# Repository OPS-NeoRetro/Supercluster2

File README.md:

# 160-Core RV32EC M.2 Supercluster

---

This supercluster consists of 10 vertically-mounted M.2 2230 modules containing 16 CH32V203C8T6 microcontrollers (not compatible with real M.2 slots) on an M.2 2280 baseboard. Host-to-cluster communication goes through a PCI Express UART controller connected to a CH32V208 on the bottom of the baseboard. Communications inside the cluster go through a custom bus that connects all 160 CH32V203 nodes and the CH32V208 baseboard controller together. Click the image below to watch the YouTube video explaining this supercluster's origins.

## Photos

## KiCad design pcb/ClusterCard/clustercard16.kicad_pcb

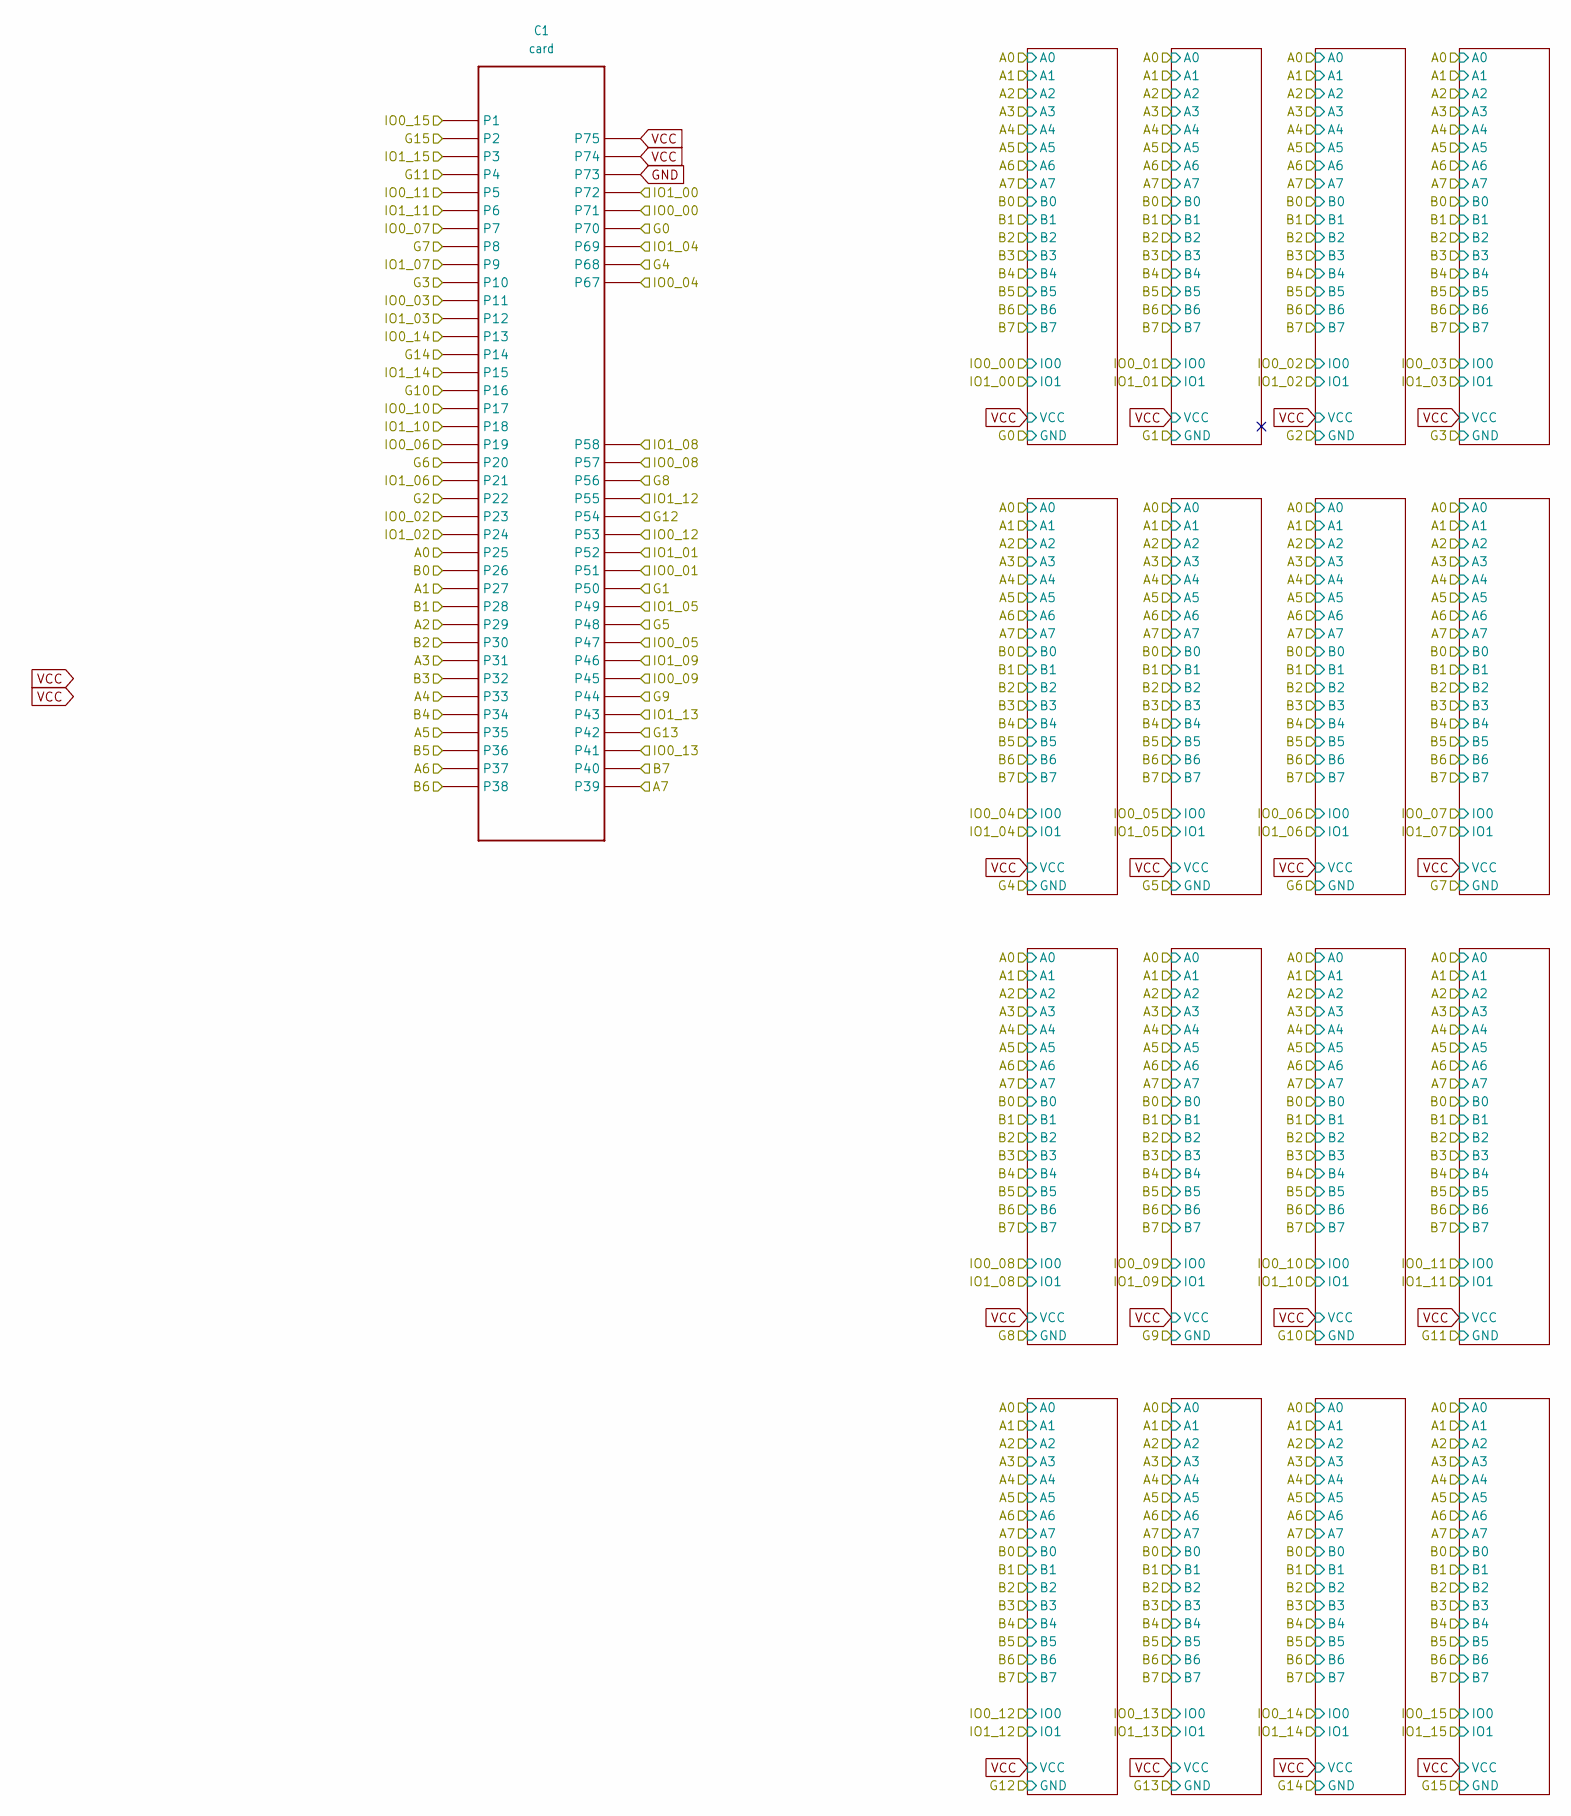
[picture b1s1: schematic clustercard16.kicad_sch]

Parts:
C1: card; M.2-M-KEY cluster card

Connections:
/A0: C1.P$25 (P25); also elsewhere on the board
/A1: C1.P$27 (P27); also elsewhere on the board
/A2: C1.P$29 (P29); also elsewhere on the board
/A3: C1.P$31 (P31); also elsewhere on the board
/A4: C1.P$33 (P33); also elsewhere on the board
/A5: C1.P$35 (P35); also elsewhere on the board
/A6: C1.P$37 (P37); also elsewhere on the board
/A7: C1.P$39 (P39); also elsewhere on the board
/B0: C1.P$26 (P26); also elsewhere on the board
/B1: C1.P$28 (P28); also elsewhere on the board
/B2: C1.P$30 (P30); also elsewhere on the board
/B3: C1.P$32 (P32); also elsewhere on the board
/B4: C1.P$34 (P34); also elsewhere on the board
/B5: C1.P$36 (P36); also elsewhere on the board
/B6: C1.P$38 (P38); also elsewhere on the board
/B7: C1.P$40 (P40); also elsewhere on the board
/G0: C1.P$70 (P70); also elsewhere on the board
/G1: C1.P$50 (P50); also elsewhere on the board
/G2: C1.P$22 (P22); also elsewhere on the board
/G3: C1.P$10 (P10); also elsewhere on the board
/G4: C1.P$68 (P68); also elsewhere on the board
/G5: C1.P$48 (P48); also elsewhere on the board
/G6: C1.P$20 (P20); also elsewhere on the board
/G7: C1.P$8 (P8); also elsewhere on the board
/G8: C1.P$56 (P56); also elsewhere on the board
/G9: C1.P$44 (P44); also elsewhere on the board
/G10: C1.P$16 (P16); also elsewhere on the board
/G11: C1.P$4 (P4); also elsewhere on the board
/G12: C1.P$54 (P54); also elsewhere on the board
/G13: C1.P$42 (P42); also elsewhere on the board
/G14: C1.P$14 (P14); also elsewhere on the board
/G15: C1.P$2 (P2); also elsewhere on the board
/IO0_00: C1.P$71 (P71); also elsewhere on the board
/IO0_01: C1.P$51 (P51); also elsewhere on the board
/IO0_02: C1.P$23 (P23); also elsewhere on the board
/IO0_03: C1.P$11 (P11); also elsewhere on the board
/IO0_04: C1.P$67 (P67); also elsewhere on the board
/IO0_05: C1.P$47 (P47); also elsewhere on the board
/IO0_06: C1.P$19 (P19); also elsewhere on the board
/IO0_07: C1.P$7 (P7); also elsewhere on the board
/IO0_08: C1.P$57 (P57); also elsewhere on the board
/IO0_09: C1.P$45 (P45); also elsewhere on the board
/IO0_10: C1.P$17 (P17); also elsewhere on the board
/IO0_11: C1.P$5 (P5); also elsewhere on the board
/IO0_12: C1.P$53 (P53); also elsewhere on the board
/IO0_13: C1.P$41 (P41); also elsewhere on the board
/IO0_14: C1.P$13 (P13); also elsewhere on the board
/IO0_15: C1.P$1 (P1); also elsewhere on the board
/IO1_00: C1.P$72 (P72); also elsewhere on the board
/IO1_01: C1.P$52 (P52); also elsewhere on the board
/IO1_02: C1.P$24 (P24); also elsewhere on the board
/IO1_03: C1.P$12 (P12); also elsewhere on the board
/IO1_04: C1.P$69 (P69); also elsewhere on the board
/IO1_05: C1.P$49 (P49); also elsewhere on the board
/IO1_06: C1.P$21 (P21); also elsewhere on the board
/IO1_07: C1.P$9 (P9); also elsewhere on the board
/IO1_08: C1.P$58 (P58); also elsewhere on the board
/IO1_09: C1.P$46 (P46); also elsewhere on the board
/IO1_10: C1.P$18 (P18); also elsewhere on the board
/IO1_11: C1.P$6 (P6); also elsewhere on the board
/IO1_12: C1.P$55 (P55); also elsewhere on the board
/IO1_13: C1.P$43 (P43); also elsewhere on the board
/IO1_14: C1.P$15 (P15); also elsewhere on the board
/IO1_15: C1.P$3 (P3); also elsewhere on the board
GND: C1.P$73 (P73)
VCC: C1.P$74 (P74), C1.P$75 (P75); also elsewhere on the board

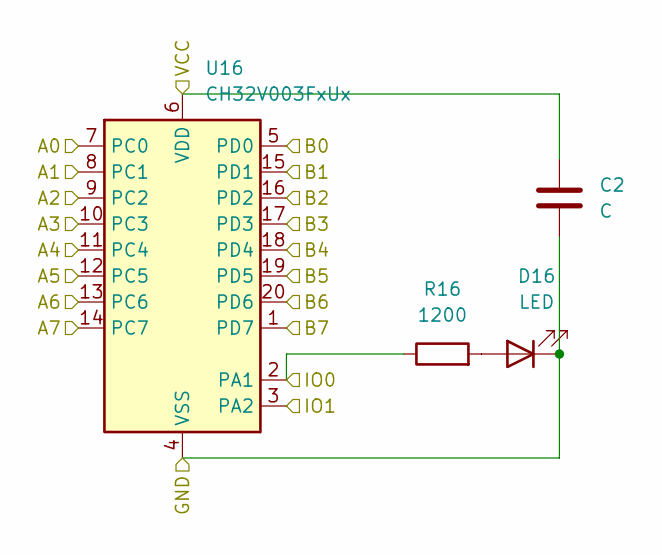
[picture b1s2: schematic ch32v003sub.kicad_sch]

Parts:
C2: C; C_0402_1005Metric
D16: LED; LED_0402_1005Metric
R16: 1200; R_0402_1005Metric
U16: CH32V003FxUx; QFN-20-1EP_3x3mm_P0.4mm_EP1.65x1.65mm_min

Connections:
/A0: U16.7 (PC0); also elsewhere on the board
/A1: U16.8 (PC1); also elsewhere on the board
/A2: U16.9 (PC2); also elsewhere on the board
/A3: U16.10 (PC3); also elsewhere on the board
/A4: U16.11 (PC4); also elsewhere on the board
/A5: U16.12 (PC5); also elsewhere on the board
/A6: U16.13 (PC6); also elsewhere on the board
/A7: U16.14 (PC7); also elsewhere on the board
/B0: U16.5 (PD0); also elsewhere on the board
/B1: U16.15 (PD1); also elsewhere on the board
/B2: U16.16 (PD2); also elsewhere on the board
/B3: U16.17 (PD3); also elsewhere on the board
/B4: U16.18 (PD4); also elsewhere on the board
/B5: U16.19 (PD5); also elsewhere on the board
/B6: U16.20 (PD6); also elsewhere on the board
/B7: U16.1 (PD7); also elsewhere on the board
/G0: C2.2, D16.1 (K), U16.4 (VSS), U16.21 (VSS); also elsewhere on the board
/IO0_00: R16.1, U16.2 (PA1); also elsewhere on the board
/IO1_00: U16.3 (PA2); also elsewhere on the board
unnamed: D16.2 (A), R16.2
VCC: C2.1, U16.6 (VDD); also elsewhere on the board

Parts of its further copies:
C3, C4, C5, C6, C7, C8, C9, C10, C11, C12, C13, C14, C15, C16, C17: C; C_0402_1005Metric
D1, D2, D3, D4, D5, D6, D7, D8, D9, D10, D11, D12, D13, D14, D15: LED; LED_0402_1005Metric
R1, R2, R3, R4, R5, R6, R7, R8, R9, R10, R11, R12, R13, R14, R15: 1200; R_0402_1005Metric
U1, U2, U3, U4, U5, U6, U7, U8, U9, U10, U11, U12, U13, U14, U15: CH32V003FxUx; QFN-20-1EP_3x3mm_P0.4mm_EP1.65x1.65mm_min

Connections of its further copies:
/A0: U1.7 (PC0), U2.7 (PC0), U3.7 (PC0), U4.7 (PC0), U5.7 (PC0), U6.7 (PC0), U7.7 (PC0), U8.7 (PC0), U9.7 (PC0), U10.7 (PC0), U11.7 (PC0), U12.7 (PC0), U13.7 (PC0), U14.7 (PC0), U15.7 (PC0); also elsewhere on the board
/A1: U1.8 (PC1), U2.8 (PC1), U3.8 (PC1), U4.8 (PC1), U5.8 (PC1), U6.8 (PC1), U7.8 (PC1), U8.8 (PC1), U9.8 (PC1), U10.8 (PC1), U11.8 (PC1), U12.8 (PC1), U13.8 (PC1), U14.8 (PC1), U15.8 (PC1); also elsewhere on the board
/A2: U1.9 (PC2), U2.9 (PC2), U3.9 (PC2), U4.9 (PC2), U5.9 (PC2), U6.9 (PC2), U7.9 (PC2), U8.9 (PC2), U9.9 (PC2), U10.9 (PC2), U11.9 (PC2), U12.9 (PC2), U13.9 (PC2), U14.9 (PC2), U15.9 (PC2); also elsewhere on the board
/A3: U1.10 (PC3), U2.10 (PC3), U3.10 (PC3), U4.10 (PC3), U5.10 (PC3), U6.10 (PC3), U7.10 (PC3), U8.10 (PC3), U9.10 (PC3), U10.10 (PC3), U11.10 (PC3), U12.10 (PC3), U13.10 (PC3), U14.10 (PC3), U15.10 (PC3); also elsewhere on the board
/A4: U1.11 (PC4), U2.11 (PC4), U3.11 (PC4), U4.11 (PC4), U5.11 (PC4), U6.11 (PC4), U7.11 (PC4), U8.11 (PC4), U9.11 (PC4), U10.11 (PC4), U11.11 (PC4), U12.11 (PC4), U13.11 (PC4), U14.11 (PC4), U15.11 (PC4); also elsewhere on the board
/A5: U1.12 (PC5), U2.12 (PC5), U3.12 (PC5), U4.12 (PC5), U5.12 (PC5), U6.12 (PC5), U7.12 (PC5), U8.12 (PC5), U9.12 (PC5), U10.12 (PC5), U11.12 (PC5), U12.12 (PC5), U13.12 (PC5), U14.12 (PC5), U15.12 (PC5); also elsewhere on the board
/A6: U1.13 (PC6), U2.13 (PC6), U3.13 (PC6), U4.13 (PC6), U5.13 (PC6), U6.13 (PC6), U7.13 (PC6), U8.13 (PC6), U9.13 (PC6), U10.13 (PC6), U11.13 (PC6), U12.13 (PC6), U13.13 (PC6), U14.13 (PC6), U15.13 (PC6); also elsewhere on the board
/A7: U1.14 (PC7), U2.14 (PC7), U3.14 (PC7), U4.14 (PC7), U5.14 (PC7), U6.14 (PC7), U7.14 (PC7), U8.14 (PC7), U9.14 (PC7), U10.14 (PC7), U11.14 (PC7), U12.14 (PC7), U13.14 (PC7), U14.14 (PC7), U15.14 (PC7); also elsewhere on the board
/B0: U1.5 (PD0), U2.5 (PD0), U3.5 (PD0), U4.5 (PD0), U5.5 (PD0), U6.5 (PD0), U7.5 (PD0), U8.5 (PD0), U9.5 (PD0), U10.5 (PD0), U11.5 (PD0), U12.5 (PD0), U13.5 (PD0), U14.5 (PD0), U15.5 (PD0); also elsewhere on the board
/B1: U1.15 (PD1), U2.15 (PD1), U3.15 (PD1), U4.15 (PD1), U5.15 (PD1), U6.15 (PD1), U7.15 (PD1), U8.15 (PD1), U9.15 (PD1), U10.15 (PD1), U11.15 (PD1), U12.15 (PD1), U13.15 (PD1), U14.15 (PD1), U15.15 (PD1); also elsewhere on the board
/B2: U1.16 (PD2), U2.16 (PD2), U3.16 (PD2), U4.16 (PD2), U5.16 (PD2), U6.16 (PD2), U7.16 (PD2), U8.16 (PD2), U9.16 (PD2), U10.16 (PD2), U11.16 (PD2), U12.16 (PD2), U13.16 (PD2), U14.16 (PD2), U15.16 (PD2); also elsewhere on the board
/B3: U1.17 (PD3), U2.17 (PD3), U3.17 (PD3), U4.17 (PD3), U5.17 (PD3), U6.17 (PD3), U7.17 (PD3), U8.17 (PD3), U9.17 (PD3), U10.17 (PD3), U11.17 (PD3), U12.17 (PD3), U13.17 (PD3), U14.17 (PD3), U15.17 (PD3); also elsewhere on the board
/B4: U1.18 (PD4), U2.18 (PD4), U3.18 (PD4), U4.18 (PD4), U5.18 (PD4), U6.18 (PD4), U7.18 (PD4), U8.18 (PD4), U9.18 (PD4), U10.18 (PD4), U11.18 (PD4), U12.18 (PD4), U13.18 (PD4), U14.18 (PD4), U15.18 (PD4); also elsewhere on the board
/B5: U1.19 (PD5), U2.19 (PD5), U3.19 (PD5), U4.19 (PD5), U5.19 (PD5), U6.19 (PD5), U7.19 (PD5), U8.19 (PD5), U9.19 (PD5), U10.19 (PD5), U11.19 (PD5), U12.19 (PD5), U13.19 (PD5), U14.19 (PD5), U15.19 (PD5); also elsewhere on the board
/B6: U1.20 (PD6), U2.20 (PD6), U3.20 (PD6), U4.20 (PD6), U5.20 (PD6), U6.20 (PD6), U7.20 (PD6), U8.20 (PD6), U9.20 (PD6), U10.20 (PD6), U11.20 (PD6), U12.20 (PD6), U13.20 (PD6), U14.20 (PD6), U15.20 (PD6); also elsewhere on the board
/B7: U1.1 (PD7), U2.1 (PD7), U3.1 (PD7), U4.1 (PD7), U5.1 (PD7), U6.1 (PD7), U7.1 (PD7), U8.1 (PD7), U9.1 (PD7), U10.1 (PD7), U11.1 (PD7), U12.1 (PD7), U13.1 (PD7), U14.1 (PD7), U15.1 (PD7); also elsewhere on the board
/G1: C3.2, D1.1 (K), U1.4 (VSS), U1.21 (VSS); also elsewhere on the board
/G2: C4.2, D2.1 (K), U2.4 (VSS), U2.21 (VSS); also elsewhere on the board
/G3: C5.2, D3.1 (K), U3.4 (VSS), U3.21 (VSS); also elsewhere on the board
/G4: C6.2, D4.1 (K), U4.4 (VSS), U4.21 (VSS); also elsewhere on the board
/G5: C7.2, D5.1 (K), U5.4 (VSS), U5.21 (VSS); also elsewhere on the board
/G6: C8.2, D6.1 (K), U6.4 (VSS), U6.21 (VSS); also elsewhere on the board
/G7: C9.2, D7.1 (K), U7.4 (VSS), U7.21 (VSS); also elsewhere on the board
/G8: C10.2, D8.1 (K), U8.4 (VSS), U8.21 (VSS); also elsewhere on the board
/G9: C11.2, D9.1 (K), U9.4 (VSS), U9.21 (VSS); also elsewhere on the board
/G10: C12.2, D10.1 (K), U10.4 (VSS), U10.21 (VSS); also elsewhere on the board
/G11: C13.2, D11.1 (K), U11.4 (VSS), U11.21 (VSS); also elsewhere on the board
/G12: C14.2, D12.1 (K), U12.4 (VSS), U12.21 (VSS); also elsewhere on the board
/G13: C15.2, D13.1 (K), U13.4 (VSS), U13.21 (VSS); also elsewhere on the board
/G14: C16.2, D14.1 (K), U14.4 (VSS), U14.21 (VSS); also elsewhere on the board
/G15: C17.2, D15.1 (K), U15.4 (VSS), U15.21 (VSS); also elsewhere on the board
/IO0_01: R1.1, U1.2 (PA1); also elsewhere on the board
/IO0_02: R2.1, U2.2 (PA1); also elsewhere on the board
/IO0_03: R3.1, U3.2 (PA1); also elsewhere on the board
/IO0_04: R4.1, U4.2 (PA1); also elsewhere on the board
/IO0_05: R5.1, U5.2 (PA1); also elsewhere on the board
/IO0_06: R6.1, U6.2 (PA1); also elsewhere on the board
/IO0_07: R7.1, U7.2 (PA1); also elsewhere on the board
/IO0_08: R8.1, U8.2 (PA1); also elsewhere on the board
/IO0_09: R9.1, U9.2 (PA1); also elsewhere on the board
/IO0_10: R10.1, U10.2 (PA1); also elsewhere on the board
/IO0_11: R11.1, U11.2 (PA1); also elsewhere on the board
/IO0_12: R12.1, U12.2 (PA1); also elsewhere on the board
/IO0_13: R13.1, U13.2 (PA1); also elsewhere on the board
/IO0_14: R14.1, U14.2 (PA1); also elsewhere on the board
/IO0_15: R15.1, U15.2 (PA1); also elsewhere on the board
/IO1_01: U1.3 (PA2); also elsewhere on the board
/IO1_02: U2.3 (PA2); also elsewhere on the board
/IO1_03: U3.3 (PA2); also elsewhere on the board
/IO1_04: U4.3 (PA2); also elsewhere on the board
/IO1_05: U5.3 (PA2); also elsewhere on the board
/IO1_06: U6.3 (PA2); also elsewhere on the board
/IO1_07: U7.3 (PA2); also elsewhere on the board
/IO1_08: U8.3 (PA2); also elsewhere on the board
/IO1_09: U9.3 (PA2); also elsewhere on the board
/IO1_10: U10.3 (PA2); also elsewhere on the board
/IO1_11: U11.3 (PA2); also elsewhere on the board
/IO1_12: U12.3 (PA2); also elsewhere on the board
/IO1_13: U13.3 (PA2); also elsewhere on the board
/IO1_14: U14.3 (PA2); also elsewhere on the board
/IO1_15: U15.3 (PA2); also elsewhere on the board
unnamed: D1.2 (A), R1.2
unnamed: D2.2 (A), R2.2
unnamed: D3.2 (A), R3.2
unnamed: D4.2 (A), R4.2
unnamed: D5.2 (A), R5.2
unnamed: D6.2 (A), R6.2
unnamed: D7.2 (A), R7.2
unnamed: D8.2 (A), R8.2
unnamed: D9.2 (A), R9.2
unnamed: D10.2 (A), R10.2
unnamed: D11.2 (A), R11.2
unnamed: D12.2 (A), R12.2
unnamed: D13.2 (A), R13.2
unnamed: D14.2 (A), R14.2
unnamed: D15.2 (A), R15.2
VCC: C3.1, C4.1, C5.1, C6.1, C7.1, C8.1, C9.1, C10.1, C11.1, C12.1, C13.1, C14.1, C15.1, C16.1, C17.1, U1.6 (VDD), U2.6 (VDD), U3.6 (VDD), U4.6 (VDD), U5.6 (VDD), U6.6 (VDD), U7.6 (VDD), U8.6 (VDD), U9.6 (VDD), U10.6 (VDD), U11.6 (VDD), U12.6 (VDD), U13.6 (VDD), U14.6 (VDD), U15.6 (VDD); also elsewhere on the board

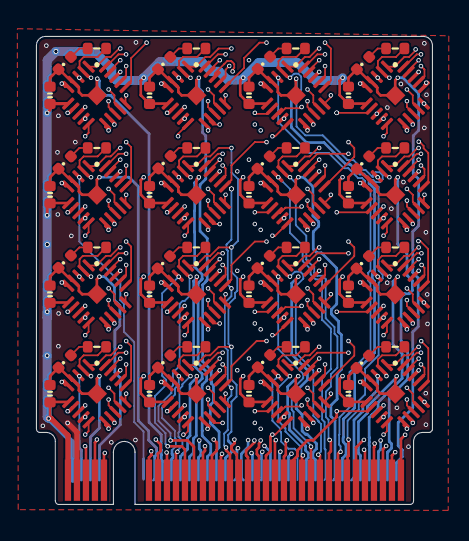
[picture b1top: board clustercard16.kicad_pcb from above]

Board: 4 copper layers, 22.0 x 26.0 mm, 65 parts (0 on the bottom side), 81 nets.

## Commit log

2025-08-21 correct cluster card files
2025-12-06 Create README.md for 160-Core RV32EC Supercluster
    Added detailed description and images for the 160-Core RV32EC M.2 Supercluster project.
2025-12-15 Initialize README with project overview and images
    Added detailed description and images for the 160-Core RV32EC M.2 Supercluster project.
2025-12-17 Add photos for README.md
2025-12-17 Update video embed to image link in README
    Replaced YouTube iframe with an image link for better rendering.
